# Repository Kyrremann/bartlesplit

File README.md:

# Bartlesplit

> Bartleby is a baby Rat Creature adopted by Fone Bone and Smiley.

Bartlesplit is based on [Cheapino](https://github.com/tompi/cheapino) by Tompi.
The original idea was to build a Cheapino with hot swaps, but it evolved into something more!

At the same time I was working on Bartlesplit, a friend of mine suggested that we try to make a splithub, letting us avoid having the Pro Micro directly on the board.
This is mostly a design choice, as it means you need to have a hub for each keyboard to avoid switching Pro Micros.
We have called the hub [The Japanese Connection](https://github.com/Kyrremann/the-japanese-connection) since it's relying on the Japanese duplex matrix.

One of the main feature of the board is the built-in tenting, so you don't need to make a case to get simple tenting.

## v1.0 built

The first version has been built, and except for the diodes on the right split needed to be flipped, everything works as expected!
Break off parts was easy to remove and then sand down the bits sticking out.
I haven't tried to break away the sixth column yet, and it will probably be a bit harder, as I only used one hole for the mouse bits.

## Render

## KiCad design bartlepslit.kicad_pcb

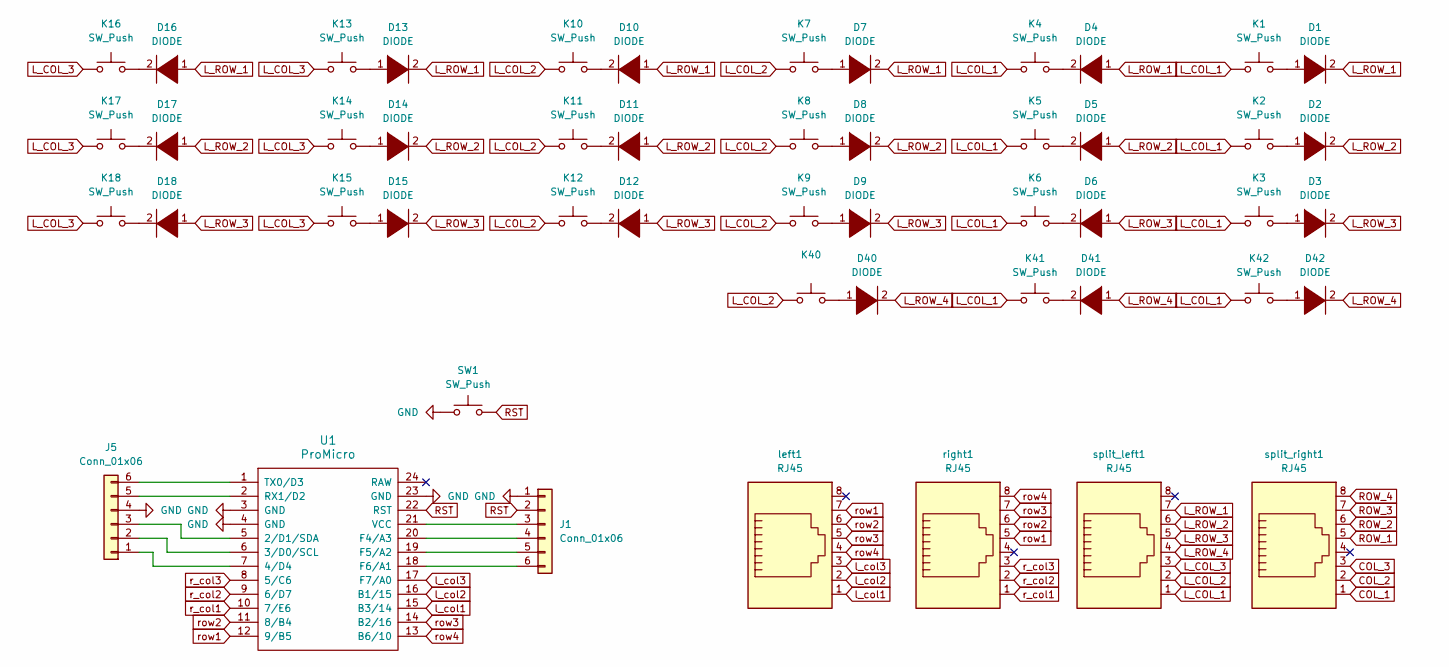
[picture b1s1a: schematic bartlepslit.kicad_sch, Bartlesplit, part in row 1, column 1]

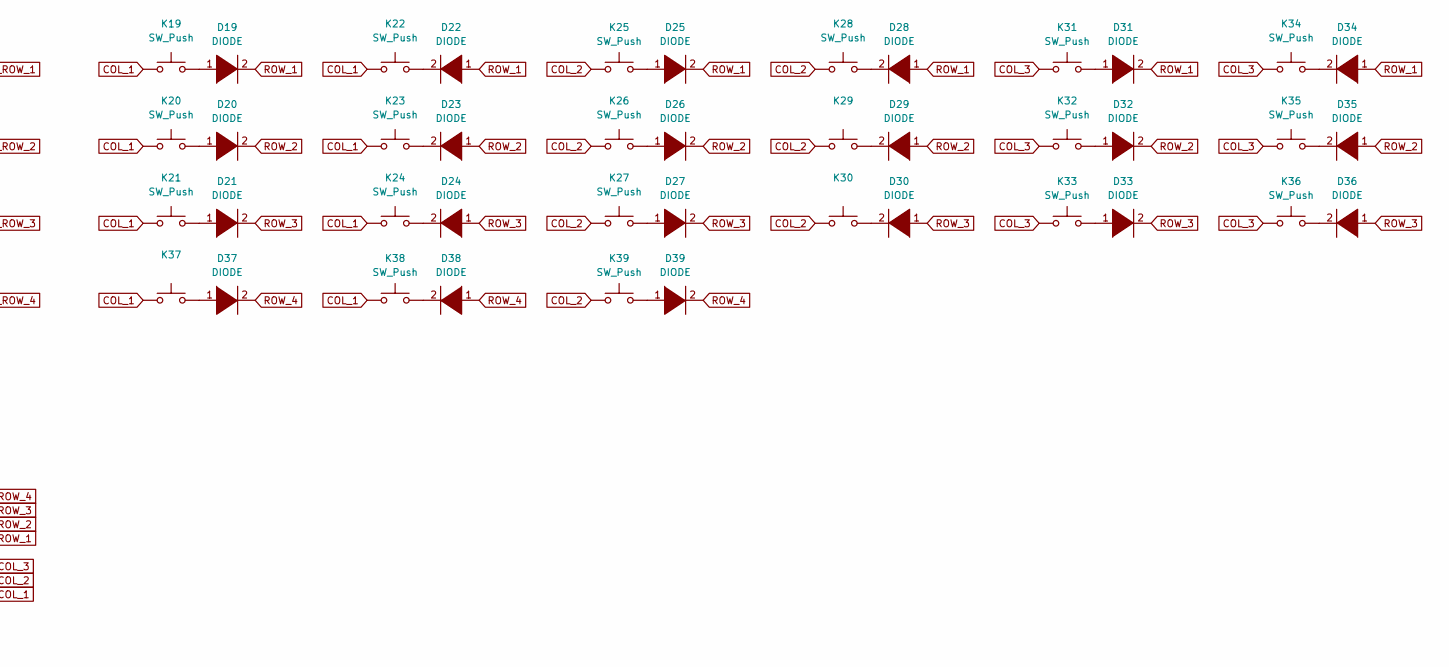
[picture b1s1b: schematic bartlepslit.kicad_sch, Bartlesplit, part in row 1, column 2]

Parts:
D1, D2, D3, D4, D5, D6, D7, D8, D9, D10, D11, D12, D13, D14, D15, D16, D17, D18, D19, D20, D21, D22, D23, D24, D25, D26, D27, D28, D29, D30, D31, D32, D33, D34, D35, D36, D37, D38, D39, D40, D41, D42: DIODE; D_SOD-123
J1, J5: Conn_01x06; PinSocket_1x06_P2.54mm_Vertical
K1, K2, K3, K4, K5, K6, K7, K8, K9, K10, K11, K12, K13, K14, K15, K16, K17, K18, K19, K20, K21, K22, K23, K24, K25, K26, K27, K28, K29, K30, K31, K32, K33, K34, K35, K36, K37, K38, K39, K40, K41, K42: SW_Push; SW_Hotswap_Kailh_MX_1.00u
SW1: SW_Push; SW_Tactile_SPST_NO_Straight_CK_PTS636Sx25SMTRLFS
U1: ProMicro; ProMicro_v3.5
left1: RJ45; RJ45_Amphenol_54602-x08_Horizontal
right1: RJ45; RJ45_Amphenol_54602-x08_Horizontal
split_left1: RJ45; RJ45_Amphenol_54602-x08_Horizontal
split_right1: RJ45; RJ45_Amphenol_54602-x08_Horizontal

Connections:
COL_1: K19.1, K20.1, K21.1, K22.1, K23.1, K24.1, K37.1, K38.1, split_right1.1
COL_2: K25.1, K26.1, K27.1, K28.1, K29.1, K30.1, K39.1, split_right1.2
COL_3: K31.1, K32.1, K33.1, K34.1, K35.1, K36.1, split_right1.3
GND: SW1.1, U1.3 (GND), U1.4 (GND), U1.23 (GND); also elsewhere on the board
L_COL_1: K1.1, K2.1, K3.1, K4.1, K5.1, K6.1, K41.1, K42.1, split_left1.1
L_COL_2: K7.1, K8.1, K9.1, K10.1, K11.1, K12.1, K40.1, split_left1.2
L_COL_3: K13.1, K14.1, K15.1, K16.1, K17.1, K18.1, split_left1.3
L_ROW_1: D1.2 (A), D4.1 (K), D7.2 (A), D10.1 (K), D13.2 (A), D16.1 (K), split_left1.7
L_ROW_2: D2.2 (A), D5.1 (K), D8.2 (A), D11.1 (K), D14.2 (A), D17.1 (K), split_left1.6
L_ROW_3: D3.2 (A), D6.1 (K), D9.2 (A), D12.1 (K), D15.2 (A), D18.1 (K), split_left1.5
L_ROW_4: D40.2 (A), D41.1 (K), D42.2 (A), split_left1.4
unnamed: D1.1 (K), K1.2
unnamed: D2.1 (K), K2.2
unnamed: D3.1 (K), K3.2
unnamed: D4.2 (A), K4.2
unnamed: D5.2 (A), K5.2
unnamed: D6.2 (A), K6.2
unnamed: D7.1 (K), K7.2
unnamed: D8.1 (K), K8.2
unnamed: D9.1 (K), K9.2
unnamed: D10.2 (A), K10.2
unnamed: D11.2 (A), K11.2
unnamed: D12.2 (A), K12.2
unnamed: D13.1 (K), K13.2
unnamed: D14.1 (K), K14.2
unnamed: D15.1 (K), K15.2
unnamed: D16.2 (A), K16.2
unnamed: D17.2 (A), K17.2
unnamed: D18.2 (A), K18.2
unnamed: D19.1 (K), K19.2
unnamed: D20.1 (K), K20.2
unnamed: D21.1 (K), K21.2
unnamed: D22.2 (A), K22.2
unnamed: D23.2 (A), K23.2
unnamed: D24.2 (A), K24.2
unnamed: D25.1 (K), K25.2
unnamed: D26.1 (K), K26.2
unnamed: D27.1 (K), K27.2
unnamed: D28.2 (A), K28.2
unnamed: D29.2 (A), K29.2
unnamed: D30.2 (A), K30.2
unnamed: D31.1 (K), K31.2
unnamed: D32.1 (K), K32.2
unnamed: D33.1 (K), K33.2
unnamed: D34.2 (A), K34.2
unnamed: D35.2 (A), K35.2
unnamed: D36.2 (A), K36.2
unnamed: D37.1 (K), K37.2
unnamed: D38.2 (A), K38.2
unnamed: D39.1 (K), K39.2
unnamed: D40.1 (K), K40.2
unnamed: D41.2 (A), K41.2
unnamed: D42.1 (K), K42.2
unnamed 53: U1.5 (2/D1/SDA); also elsewhere on the board
unnamed 54: U1.6 (3/D0/SCL); also elsewhere on the board
unnamed 55: U1.7 (4/D4); also elsewhere on the board
unnamed 56: U1.20 (F4/A3); also elsewhere on the board
unnamed 57: U1.19 (F5/A2); also elsewhere on the board
unnamed 58: U1.18 (F6/A1); also elsewhere on the board
unnamed 59: U1.2 (RX1/D2); also elsewhere on the board
unnamed 60: U1.1 (TX0/D3); also elsewhere on the board
unnamed 61: U1.21 (VCC); also elsewhere on the board
ROW_1: D19.2 (A), D22.1 (K), D25.2 (A), D28.1 (K), D31.2 (A), D34.1 (K), split_right1.5
ROW_2: D20.2 (A), D23.1 (K), D26.2 (A), D29.1 (K), D32.2 (A), D35.1 (K), split_right1.6
ROW_3: D21.2 (A), D24.1 (K), D27.2 (A), D30.1 (K), D33.2 (A), D36.1 (K), split_right1.7
ROW_4: D37.2 (A), D38.1 (K), D39.2 (A), split_right1.8
RST: SW1.2, U1.22 (RST); also elsewhere on the board
l_col1: U1.15 (B3/14); also elsewhere on the board
l_col2: U1.16 (B1/15); also elsewhere on the board
l_col3: U1.17 (F7/A0); also elsewhere on the board
r_col1: U1.10 (7/E6); also elsewhere on the board
r_col2: U1.9 (6/D7); also elsewhere on the board
r_col3: U1.8 (5/C6); also elsewhere on the board
row1: U1.12 (9/B5); also elsewhere on the board
row2: U1.11 (8/B4); also elsewhere on the board
row3: U1.14 (B2/16); also elsewhere on the board
row4: U1.13 (B6/10); also elsewhere on the board

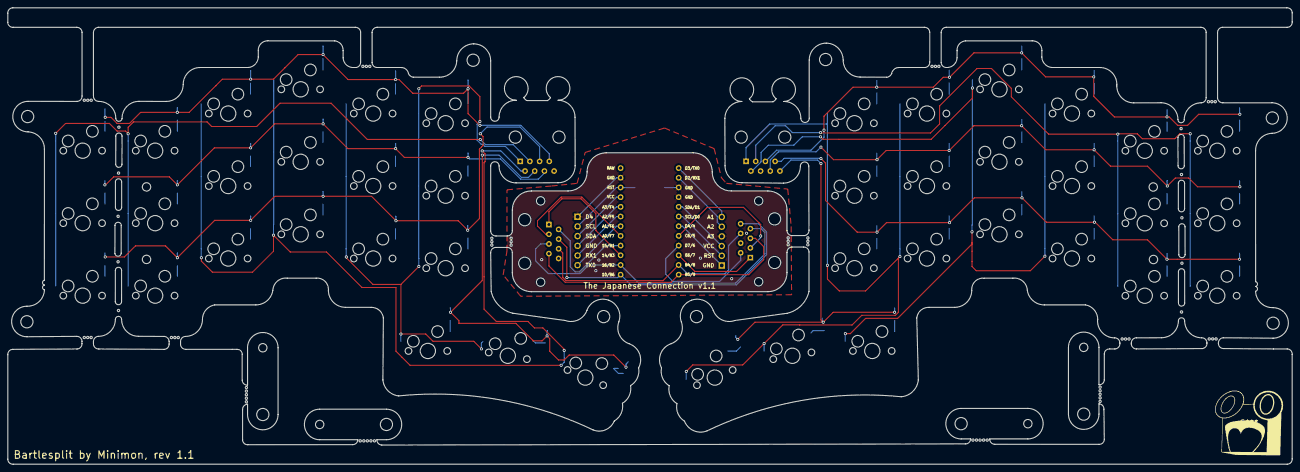
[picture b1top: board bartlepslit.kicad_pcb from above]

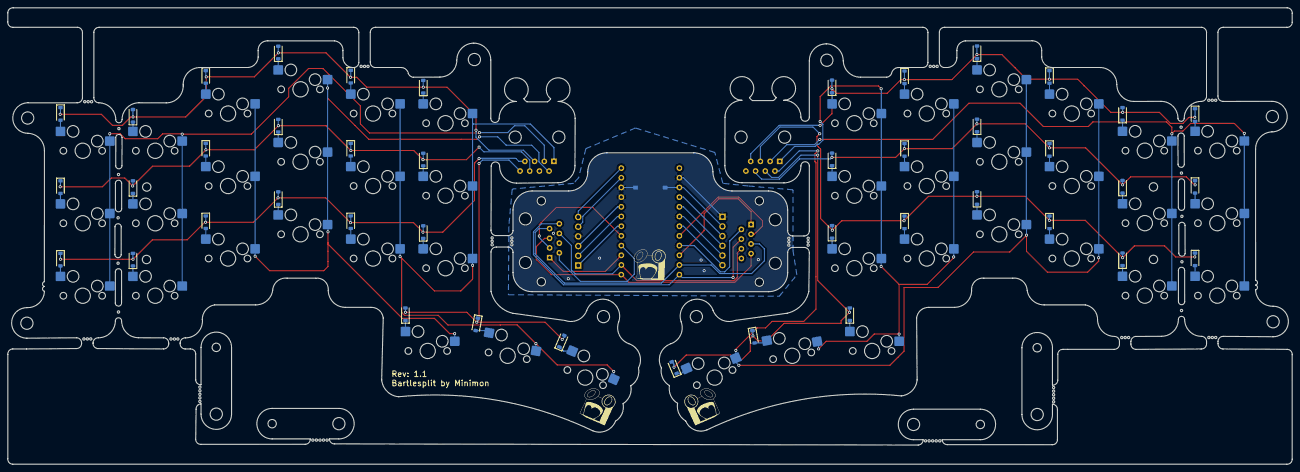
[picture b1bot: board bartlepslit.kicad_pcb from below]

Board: 2 copper layers, 336.7 x 119.6 mm, 92 parts (45 on the bottom side), 77 nets.

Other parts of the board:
tjc_j1, tjc_j2: Conn_01x06; PinSocket_1x06_P2.54mm_Vertical
tjc_left2: RJ45; RJ45_Amphenol_54602-x08_Horizontal
tjc_right2: RJ45; RJ45_Amphenol_54602-x08_Horizontal

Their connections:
GND: tjc_j1.4, tjc_j2.1; also elsewhere on the board
unnamed 53: tjc_j1.3; also elsewhere on the board
unnamed 54: tjc_j1.2; also elsewhere on the board
unnamed 55: tjc_j1.1; also elsewhere on the board
unnamed 56: tjc_j2.4; also elsewhere on the board
unnamed 57: tjc_j2.5; also elsewhere on the board
unnamed 58: tjc_j2.6; also elsewhere on the board
unnamed 59: tjc_j1.5; also elsewhere on the board
unnamed 60: tjc_j1.6; also elsewhere on the board
unnamed 61: tjc_j2.3; also elsewhere on the board
RST: tjc_j2.2; also elsewhere on the board
l_col1: tjc_left2.1; also elsewhere on the board
l_col2: tjc_left2.2; also elsewhere on the board
l_col3: tjc_left2.3; also elsewhere on the board
r_col1: tjc_right2.1; also elsewhere on the board
r_col2: tjc_right2.2; also elsewhere on the board
r_col3: tjc_right2.3; also elsewhere on the board
row1: tjc_left2.7, tjc_right2.5; also elsewhere on the board
row2: tjc_left2.6, tjc_right2.6; also elsewhere on the board
row3: tjc_left2.5, tjc_right2.7; also elsewhere on the board
row4: tjc_left2.4, tjc_right2.8; also elsewhere on the board

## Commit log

2023-10-19 feat: init commit
2023-10-19 [ImgBot] Optimize images
    /images/bartlesplit-v1.png -- 284.64kb -> 266.76kb (6.28%)
2023-10-26 feat: fixed orientation of diodes
2023-10-26 feat: removed unncessary silkprints
2023-10-26 feat: optimized break off parts
2023-10-26 feat: added missing reset switch
2023-10-26 feat: bump revison to v1.1
2023-10-26 doc: some info about v1.0
